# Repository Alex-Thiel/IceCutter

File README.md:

# IceCutter

This is the PCB and Code for the Temperature Controlled Ice Cutter for EEE4022S.

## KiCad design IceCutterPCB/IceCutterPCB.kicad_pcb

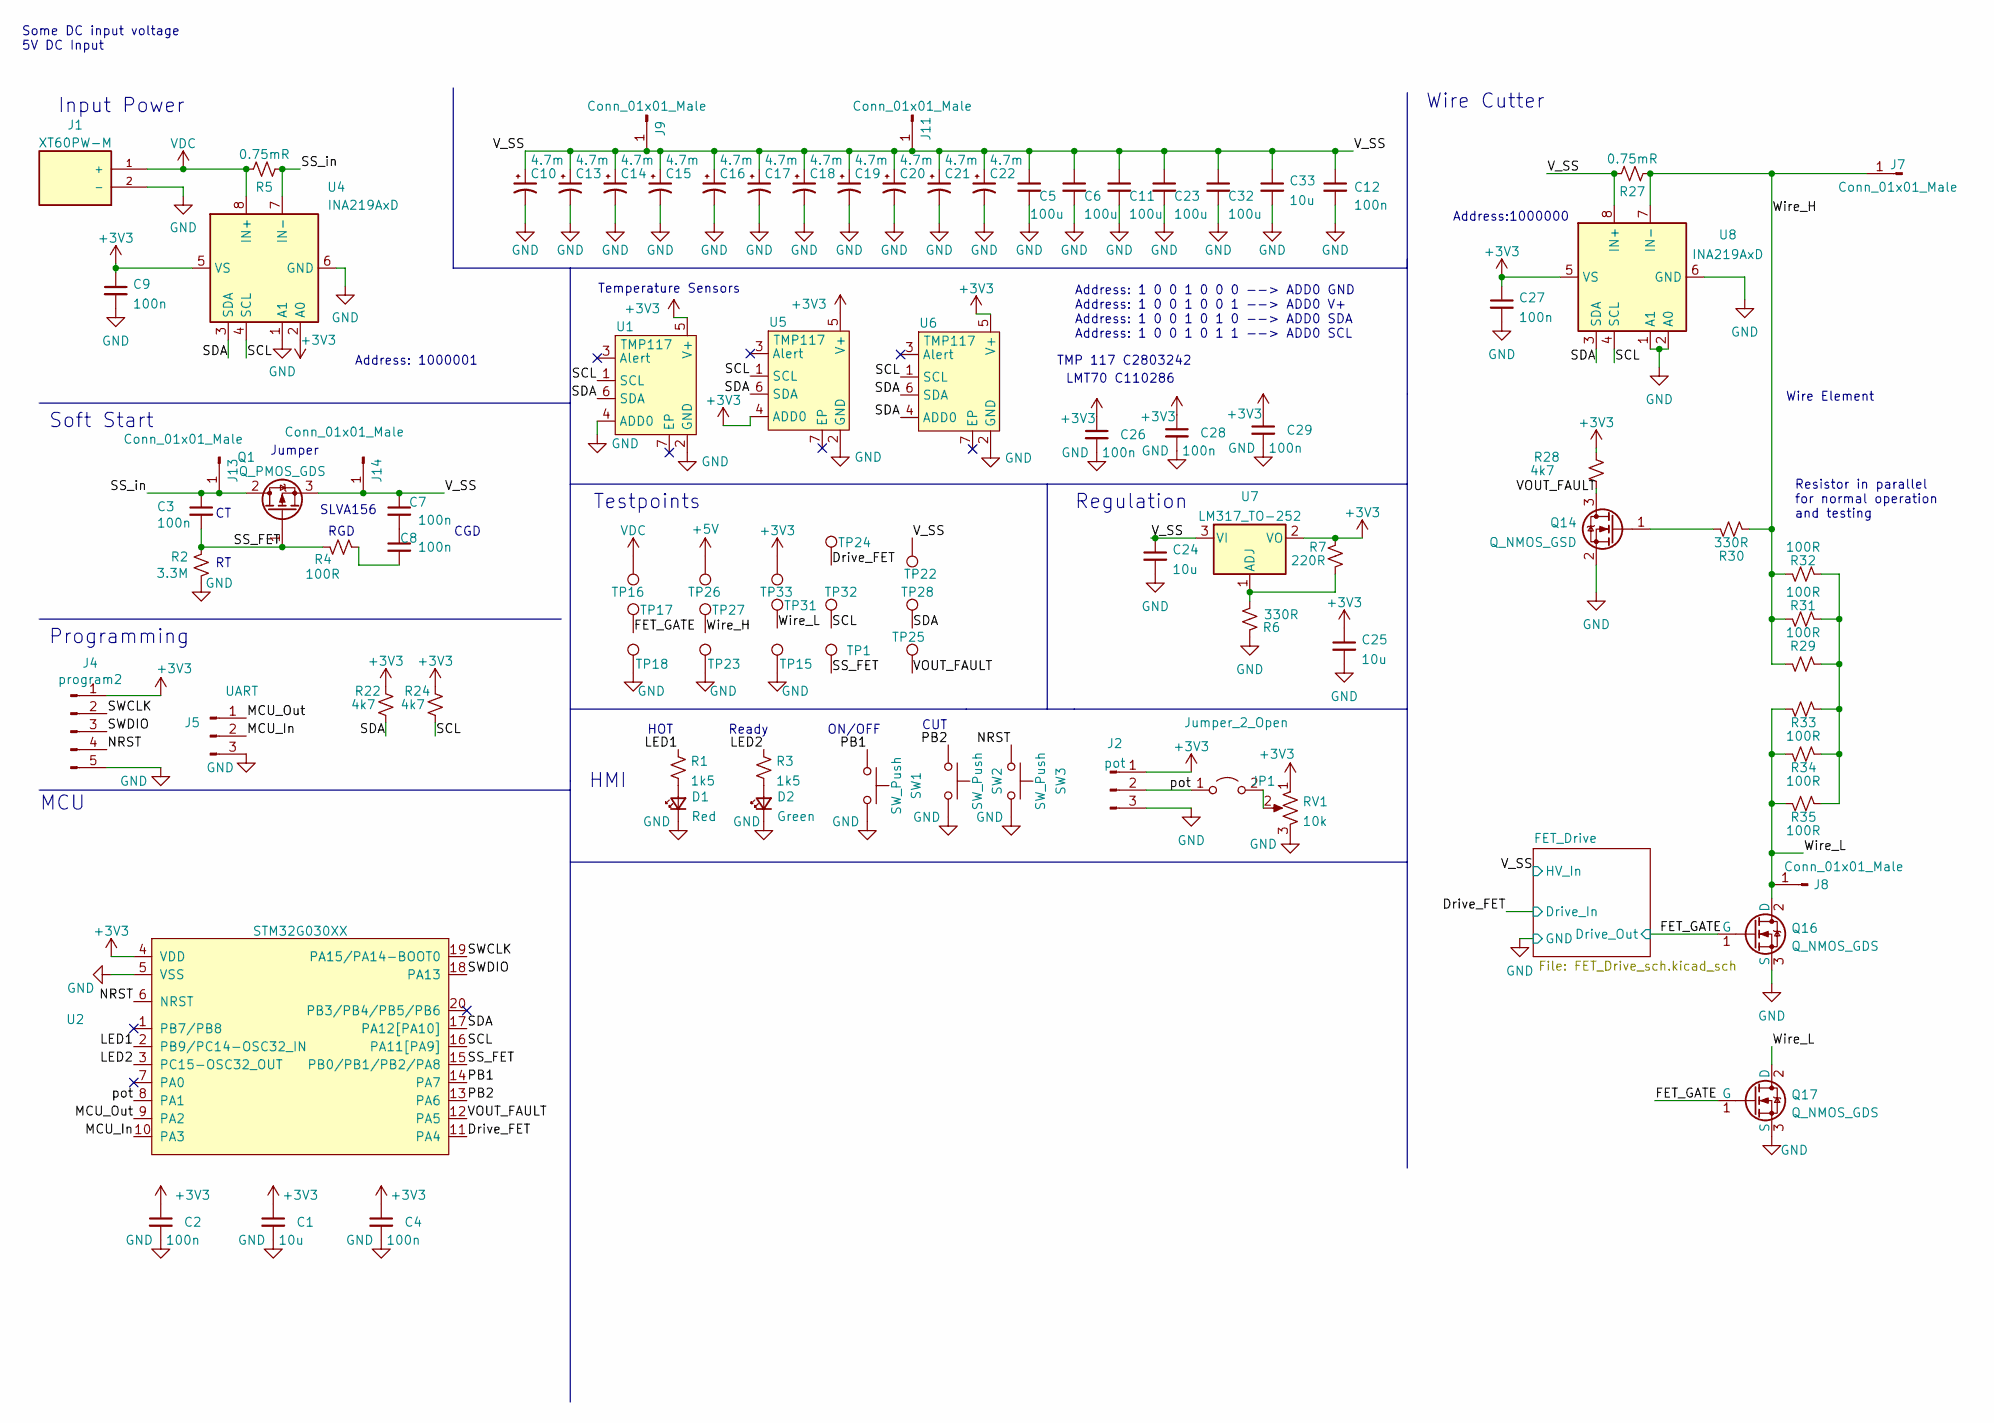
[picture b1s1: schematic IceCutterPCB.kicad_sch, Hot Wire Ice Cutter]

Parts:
C1, C24, C25, C33: 10u; C_0603_1608Metric; LCSC C96446
C2, C3, C4, C7, C8, C9, C12, C26, C27, C28, C29: 100n; C_0402_1005Metric; LCSC C307331
C5, C6, C11, C23, C32: 100u; C_1206_3216Metric; LCSC C15008
C10, C13, C14, C15, C16, C17, C18, C19, C20, C21, C22: 4.7m; CP_Radial_D14.0mm_P5.00mm
D1: Red; D_0603_1608Metric; LCSC C2286
D2: Green; D_0603_1608Metric; LCSC C72043
J1: XT60PW-M; AMASS_XT60PW-M; PARTREV V1.2
J2: pot; PinHeader_1x03_P2.54mm_Vertical
J4: program2; PinHeader_1x05_P2.54mm_Vertical
J5: UART; PinHeader_1x03_P2.54mm_Vertical
J7, J8, J9, J11, J13, J14: Conn_01x01_Male; SMD_Pad_15x10
JP1: Jumper_2_Open; SolderJumper-2_P1.3mm_Open_RoundedPad1.0x1.5mm
Q1: Q_PMOS_GDS; TO-252-2
Q14: Q_NMOS_GSD; SOT-23; LCSC C20917
Q16, Q17: Q_NMOS_GDS; TO-252-2; LCSC C709962
R1, R3: 1k5; R_0402_1005Metric; LCSC C25867
R2: 3.3M; R_0402_1005Metric; LCSC C25741
R4: 100R; R_0402_1005Metric; LCSC C25076
R5, R27: 0.75mR; res_5930
R6, R30: 330R; R_0402_1005Metric; LCSC C25104
R7: 220R; R_0402_1005Metric; LCSC C25091
R22, R24, R28: 4k7; R_0402_1005Metric; LCSC C25900
R29, R31, R32, R33, R34, R35: 100R; R_1206_3216Metric; LCSC C17901
RV1: 10k; RK09_THT_Pot_C209770; LCSC C209770
SW1, SW2, SW3: SW_Push; SW_SPST_TL3342; LCSC C318884
TP1, TP15, TP16, TP17, TP18, TP22, TP23, TP24, TP25, TP26, TP27, TP28, TP31, TP32, TP33: TestPoint; TestPoint_Pad_D2.0mm
U1, U5, U6: TMP117; WSON-6-1EP_2x2mm_P0.65mm_EP1x1.6mm; LCSC C2803242
U2: STM32G030XX; TSSOP-20_4.4x6.5mm_P0.65mm; LCSC C529330
U4, U8: INA219AxD; SOIC-8_3.9x4.9mm_P1.27mm; LCSC C138706
U7: LM317_TO-252; TO-252-2; LCSC C75510

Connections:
+3V3: C1.1, C2.1, C4.1, C9.1, C25.1, C26.1, C27.1, C28.1, C29.1, J2.1, J4.1, R7.2, R22.2, R24.2, R28.2, RV1.1, TP33.1, U1.5 (V+), U2.4 (VDD), U4.2 (A0), U4.5 (VS), U5.4 (ADD0), U5.5 (V+), U6.5 (V+), U7.2 (VO), U8.5 (VS)
+5V: TP26.1
/Drive_FET: TP24.1, U2.11 (PA4); also elsewhere on the board
/FET_GATE: Q16.1 (G), Q17.1 (G), TP17.1; also elsewhere on the board
/LED1: R1.1, U2.2 (PB9/PC14-OSC32_IN)
/LED2: R3.1, U2.3 (PC15-OSC32_OUT)
/MCU_In: J5.2, U2.10 (PA3)
/MCU_Out: J5.1, U2.9 (PA2)
/NRST: J4.4, SW3.1, U2.6 (NRST)
/PB1: SW1.1, U2.14 (PA7)
/PB2: SW2.1, U2.13 (PA6)
/SCL: R24.1, TP32.1, U1.1 (SCL), U2.16 (PA11[PA9]), U4.4 (SCL), U5.1 (SCL), U6.1 (SCL), U8.4 (SCL)
/SDA: R22.1, TP28.1, U1.6 (SDA), U2.17 (PA12[PA10]), U4.3 (SDA), U5.6 (SDA), U6.4 (ADD0), U6.6 (SDA), U8.3 (SDA)
/SS_FET: C3.2, Q1.1 (G), R2.1, R4.1, TP1.1, U2.15 (PB0/PB1/PB2/PA8)
/SS_in: C3.1, J13.1, Q1.2 (D), R5.2, U4.7 (IN-)
/SWCLK: J4.2, U2.19 (PA15/PA14-BOOT0)
/SWDIO: J4.3, U2.18 (PA13)
/VOUT_FAULT: Q14.3 (D), R28.1, TP25.1, U2.12 (PA5)
/V_SS: C5.1, C6.1, C7.1, C10.1, C11.1, C12.1, C13.1, C14.1, C15.1, C16.1, C17.1, C18.1, C19.1, C20.1, C21.1, C22.1, C23.1, C24.1, C32.1, C33.1, J9.1, J11.1, J14.1, Q1.3 (S), R27.1, TP22.1, U7.3 (VI), U8.8 (IN+); also elsewhere on the board
/Wire_H: J7.1, R27.2, R29.1, R30.1, R31.1, R32.1, TP27.1, U8.7 (IN-)
/Wire_L: J8.1, Q16.2 (D), Q17.2 (D), R33.2, R34.2, R35.2, TP31.1
/pot: J2.2, JP1.1 (A), U2.8 (PA1)
GND: C1.2, C2.2, C4.2, C5.2, C6.2, C9.2, C10.2, C11.2, C12.2, C13.2, C14.2, C15.2, C16.2, C17.2, C18.2, C19.2, C20.2, C21.2, C22.2, C23.2, C24.2, C25.2, C26.2, C27.2, C28.2, C29.2, C32.2, C33.2, D1.1 (K), D2.1 (K), J1.2 (-), J2.3, J4.5, J5.3, Q14.2 (S), Q16.3 (S), Q17.3 (S), R2.2, R6.1, RV1.3, SW1.2, SW2.2, SW3.2, TP15.1, TP18.1, TP23.1, U1.2 (GND), U1.4 (ADD0), U2.5 (VSS), U4.1 (A1), U4.6 (GND), U5.2 (GND), U6.2 (GND), U8.1 (A1), U8.2 (A0), U8.6 (GND); also elsewhere on the board
unnamed: C7.2, C8.1
unnamed: C8.2, R4.2
unnamed: D1.2 (A), R1.2
unnamed: D2.2 (A), R3.2
unnamed: JP1.2 (B), RV1.2
unnamed: Q14.1 (G), R30.2
unnamed: R6.2, R7.1, U7.1 (ADJ)
unnamed: R29.2, R31.2, R32.2, R33.1, R34.1, R35.1
VDC: J1.1 (+), R5.1, TP16.1, U4.8 (IN+)

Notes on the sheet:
CUT
Resistor in parallel for normal operation and testing
Some DC input voltage 5V DC Input
CGD
LMT70 C110286
Jumper
Testpoints
HOT
Input Power
Wire Element
HMI
Soft Start
SLVA156
Programming
Address: 1 0 0 1 0 0 0 --> ADD0 GND Address: 1 0 0 1 0 0 1 --> ADD0 V+ Address: 1 0 0 1 0 1 0 --> ADD0 SDA Address: 1 0 0 1 0 1 1 --> ADD0 SCL
Address: 1000001
MCU
Ready
Wire Cutter
ON/OFF
TMP 117 C2803242
Regulation
Address:1000000
Temperature Sensors
RGD

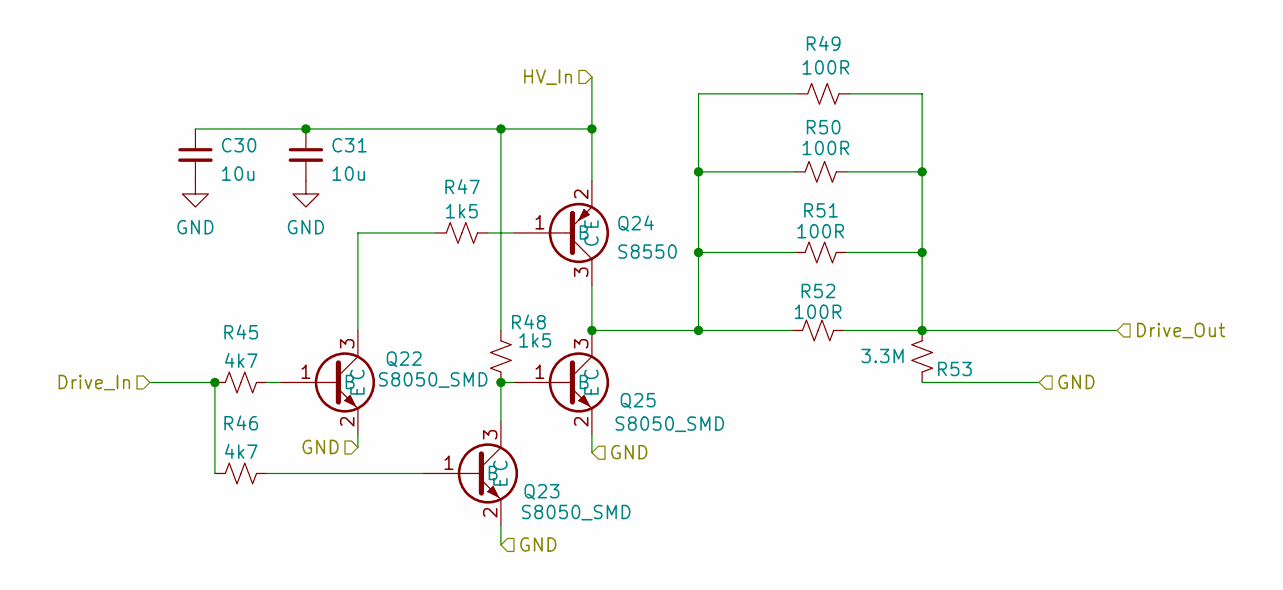
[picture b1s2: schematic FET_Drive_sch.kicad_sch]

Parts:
C30, C31: 10u; C_0603_1608Metric; LCSC C96446
Q22, Q23, Q25: S8050_SMD; SOT-23; LCSC C2150
Q24: S8550; SOT-23; LCSC C8542
R45, R46: 4k7; R_0402_1005Metric; LCSC C25900
R47, R48: 1k5; R_0402_1005Metric; LCSC C25867
R49, R50, R51, R52: 100R; R_0402_1005Metric; LCSC C25076
R53: 3.3M; R_0402_1005Metric; LCSC C25741

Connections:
/Drive_FET: R45.1, R46.1; also elsewhere on the board
/FET_GATE: R49.2, R50.2, R51.2, R52.2, R53.1; also elsewhere on the board
/V_SS: C30.1, C31.1, Q24.2 (E), R48.2; also elsewhere on the board
GND: C30.2, C31.2, Q22.2 (E), Q23.2 (E), Q25.2 (E), R53.2; also elsewhere on the board
unnamed: Q22.1 (B), R45.2
unnamed: Q22.3 (C), R47.1
unnamed: Q23.1 (B), R46.2
unnamed: Q23.3 (C), Q25.1 (B), R48.1
unnamed: Q24.1 (B), R47.2
unnamed: Q24.3 (C), Q25.3 (C), R49.1, R50.1, R51.1, R52.1

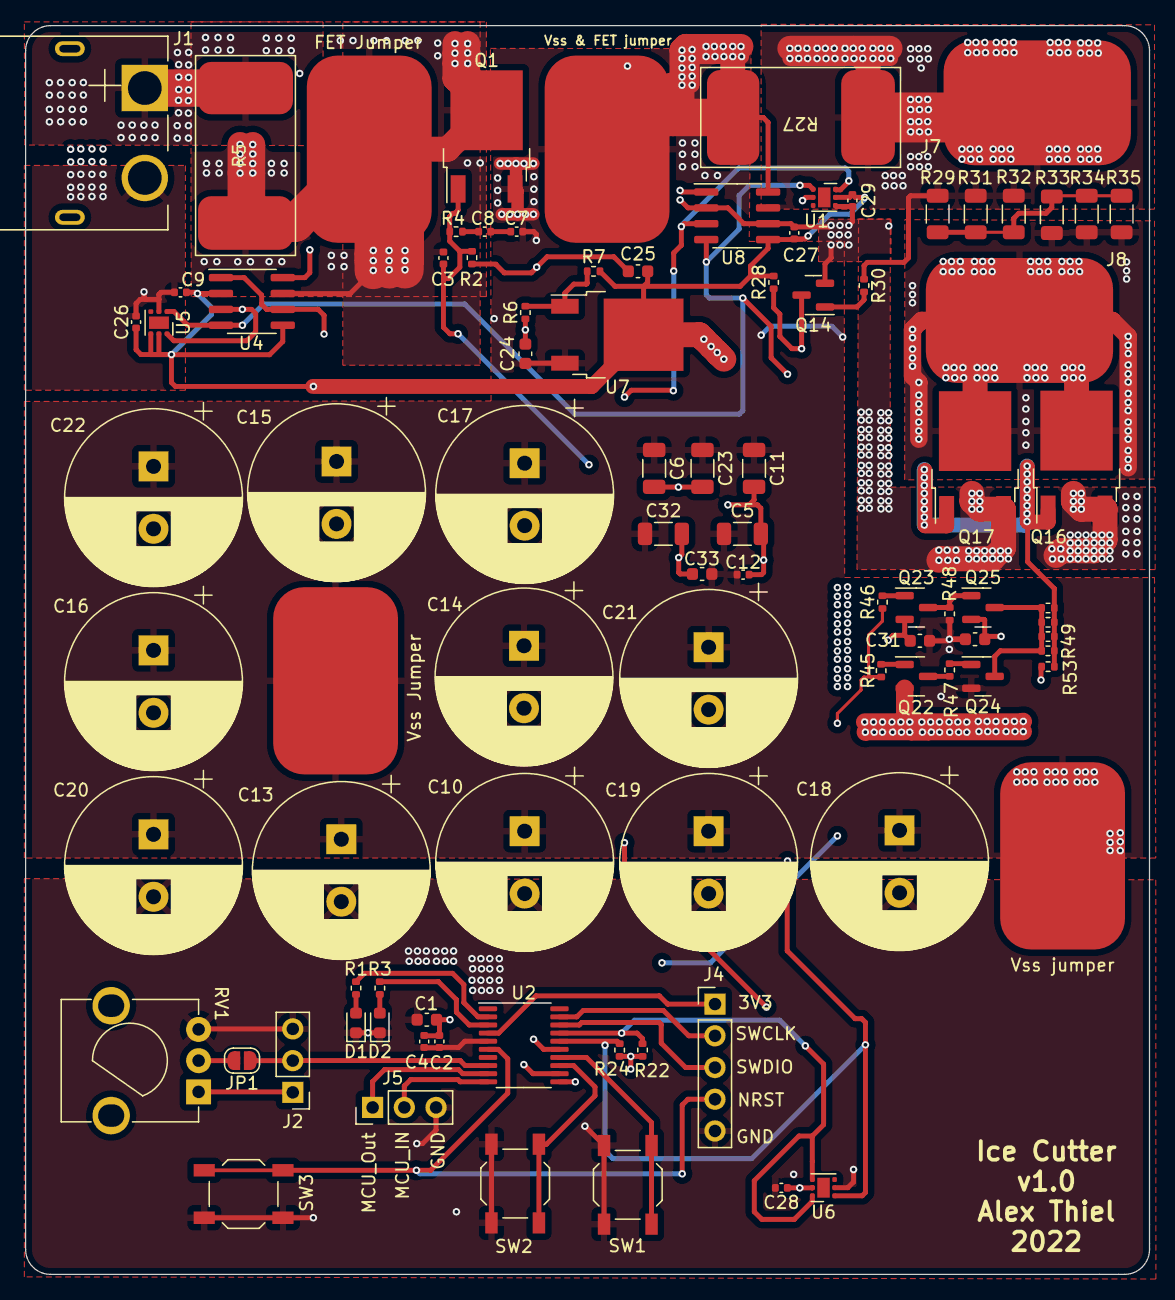
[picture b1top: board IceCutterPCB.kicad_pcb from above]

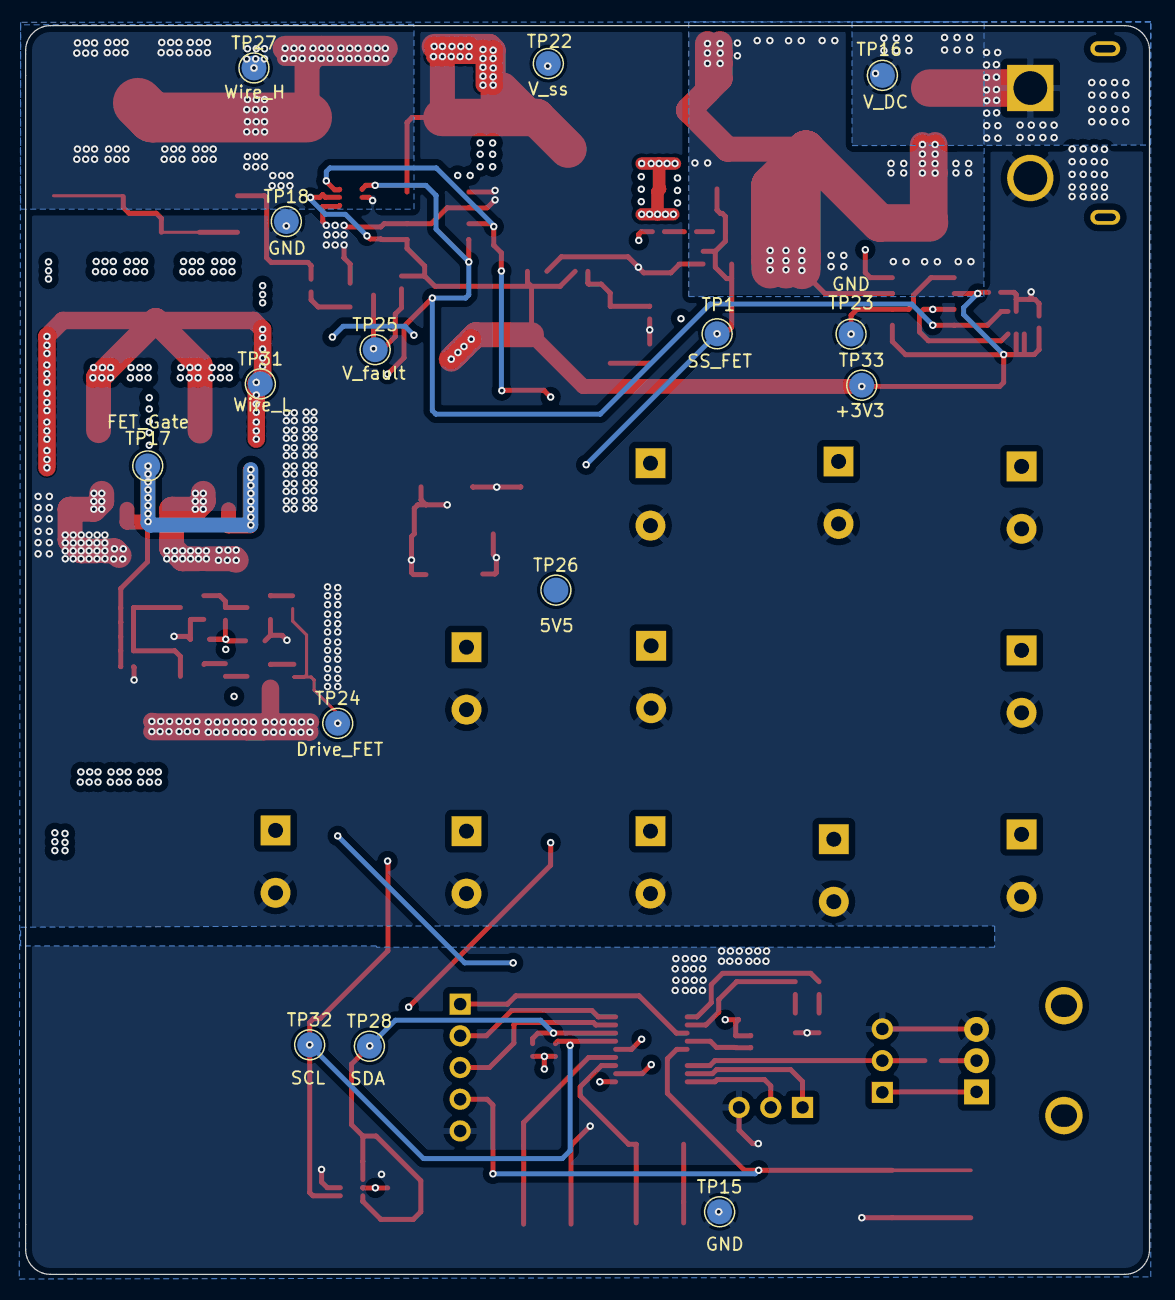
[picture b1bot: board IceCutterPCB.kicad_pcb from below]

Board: 4 copper layers, 90.0 x 100.0 mm, 107 parts (15 on the bottom side), 37 nets.

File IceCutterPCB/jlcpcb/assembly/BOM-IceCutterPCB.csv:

Comment,Designator,Footprint,LCSC
INA219AxD,"U4,U8",SOIC-8_3.9x4.9mm_P1.27mm,C138706
100u,"C11,C23,C32,C5,C6",C_1206_3216Metric,C15008
Q_PMOS_GDS,Q1,TO-252-2,C165222
100R,"R29,R31,R32,R33,R34,R35",R_1206_3216Metric,C17901
Q_NMOS_GSD,Q14,SOT-23,C20917
10k,RV1,RK09_THT_Pot_C209770,C209770
S8050_SMD,"Q22,Q23,Q25",SOT-23,C2150
3.3M,"R2,R53",R_0402_1005Metric,C227368
Red,D1,D_0603_1608Metric,C2286
100R,"R4,R49,R50,R51,R52",R_0402_1005Metric,C25076
220R,R7,R_0402_1005Metric,C25091
330R,"R30,R6",R_0402_1005Metric,C25104
1k5,"R1,R3,R47,R48",R_0402_1005Metric,C25867
4k7,"R22,R24,R28,R45,R46",R_0402_1005Metric,C25900
TMP117,"U1,U5,U6",WSON-6-1EP_2x2mm_P0.65mm_EP1x1.6mm,C2803242
100n,"C12,C2,C26,C27,C28,C29,C3,C4,C7,C8,C9",C_0402_1005Metric,C307331
SW_Push,"SW1,SW2,SW3",SW_SPST_TL3342,C318884
0.75mR,"R27,R5",res_5930,C495778
STM32G030XX,U2,TSSOP-20_4.4x6.5mm_P0.65mm,C529330
Q_NMOS_GDS,"Q16,Q17",TO-252-2,C709962
Green,D2,D_0603_1608Metric,C72043
LM317_TO-252,U7,TO-252-2,C75510
S8550,Q24,SOT-23,C8542
10u,"C1,C24,C25,C30,C31,C33",C_0603_1608Metric,C96446
XT60PW-M,J1,AMASS_XT60PW-M,C98732

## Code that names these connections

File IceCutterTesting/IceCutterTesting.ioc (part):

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Mcu.Name=STM32G030F6Px
Mcu.Package=TSSOP20
Mcu.UserName=STM32G030F6Px
PA1.Mode=IN1
PA1.Signal=ADC1_IN1
PA11\ [PA9].Mode=I2C
PA11\ [PA9].Signal=I2C2_SCL
PA12\ [PA10].Mode=I2C
PA12\ [PA10].Signal=I2C2_SDA
PA13.Mode=Serial_Wire
PA13.Signal=SYS_SWDIO
PA14-BOOT0.Mode=Serial_Wire
PA14-BOOT0.Signal=SYS_SWCLK
PA14-BOOT0__PA15.StandardMode=true
PA2.Mode=Asynchronous
PA2.Signal=USART2_TX
PA3.Mode=Asynchronous
PA3.Signal=USART2_RX
PA4.Signal=S_TIM14_CH1
PA5.Signal=GPIO_Input
PA6.GPIOParameters=GPIO_PuPd,GPIO_ModeDefaultEXTI
PA6.GPIO_ModeDefaultEXTI=GPIO_MODE_IT_FALLING
PA6.GPIO_PuPd=GPIO_PULLUP
PA6.Signal=GPXTI6
PA7.GPIOParameters=GPIO_PuPd,GPIO_ModeDefaultEXTI
PA7.GPIO_ModeDefaultEXTI=GPIO_MODE_IT_FALLING
PA7.GPIO_PuPd=GPIO_PULLUP
PA7.Signal=GPXTI7
PB0.GPIOParameters=GPIO_Speed,PinState
PB0.GPIO_Speed=GPIO_SPEED_FREQ_VERY_HIGH
PB0.PinState=GPIO_PIN_SET
PB0.Signal=GPIO_Output
PB0__PB1__PB2__PA8.StandardMode=true
PB3__PB4__PB5__PB6.StandardMode=true
PB5.Signal=S_TIM3_CH2
PB7__PB8.StandardMode=true
PB9.GPIOParameters=GPIO_Speed,PinState,GPIO_PuPd,GPIO_ModeDefaultOutputPP,GPIO_FM9
PB9.GPIO_FM9=SYSCFG_FASTMODEPLUS_PB9
PB9.GPIO_ModeDefaultOutputPP=GPIO_MODE_OUTPUT_PP
PB9.GPIO_PuPd=GPIO_NOPULL
PB9.GPIO_Speed=GPIO_SPEED_FREQ_VERY_HIGH
PB9.PinState=GPIO_PIN_SET
PB9.Signal=GPIO_Output
PC14-OSC32_IN\ (PC14)__PB9.StandardMode=true
PC15-OSC32_OUT\ (PC15).GPIOParameters=PinState,GPIO_PuPd,GPIO_ModeDefaultOutputPP
PC15-OSC32_OUT\ (PC15).GPIO_ModeDefaultOutputPP=GPIO_MODE_OUTPUT_PP
PC15-OSC32_OUT\ (PC15).GPIO_PuPd=GPIO_PULLUP
PC15-OSC32_OUT\ (PC15).PinState=GPIO_PIN_SET
PC15-OSC32_OUT\ (PC15).Signal=GPIO_Output
RCC.HSE_VALUE=8000000
RCC.SYSCLKFreq_VALUE=16000000
board=custom

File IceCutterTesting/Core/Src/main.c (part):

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#define RED_LED_state	GPIOB
#define GREEN_LED 		GPIO_PIN_15
#define GREEN_LED_state	GPIOC
#define SS_FET			GPIO_PIN_0
#define SS_FET_state	GPIOB
#define DRIVE_FET 		GPIO_PIN_4
#define DRIVE_FET_state	GPIOA
#define SW2 			GPIO_PIN_6
#define SW2_state		GPIOA
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
  //current_state = POWER_ON;
  startup_initialisation();
  HAL_GPIO_WritePin(GPIOB,SS_FET,GPIO_PIN_SET);
  /* USER CODE END 2 */

  /* Infinite loop */
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  /*Configure GPIO pin Output Level */
  HAL_GPIO_WritePin(GPIOC, GPIO_PIN_15, GPIO_PIN_SET);

  /*Configure GPIO pins : PB9 PB0 */
  GPIO_InitStruct.Pin = GPIO_PIN_9|GPIO_PIN_0;
  GPIO_InitStruct.Mode = GPIO_MODE_OUTPUT_PP;
  GPIO_InitStruct.Pull = GPIO_NOPULL;
  GPIO_InitStruct.Speed = GPIO_SPEED_FREQ_VERY_HIGH;
  HAL_GPIO_Init(GPIOB, &GPIO_InitStruct);

  /*Configure GPIO pin : PC15 */
  GPIO_InitStruct.Pin = GPIO_PIN_15;
  GPIO_InitStruct.Mode = GPIO_MODE_OUTPUT_PP;
  GPIO_InitStruct.Pull = GPIO_PULLUP;
  GPIO_InitStruct.Speed = GPIO_SPEED_FREQ_LOW;
  HAL_GPIO_Init(GPIOC, &GPIO_InitStruct);

  /*Configure GPIO pin : PA5 */
  GPIO_InitStruct.Pin = GPIO_PIN_5;
  GPIO_InitStruct.Mode = GPIO_MODE_INPUT;
  GPIO_InitStruct.Pull = GPIO_NOPULL;
  HAL_GPIO_Init(GPIOA, &GPIO_InitStruct);

  /*Configure GPIO pins : PA6 PA7 */
  GPIO_InitStruct.Pin = GPIO_PIN_6|GPIO_PIN_7;
  GPIO_InitStruct.Mode = GPIO_MODE_IT_FALLING;
  GPIO_InitStruct.Pull = GPIO_PULLUP;
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 */
 void SS_charge(){
	 uint8_t counter = 0;
	 HAL_GPIO_WritePin(GPIOB,SS_FET,GPIO_PIN_RESET);
	 while(HAL_GPIO_ReadPin(GPIOB,SS_FET) == GPIO_PIN_RESET){
		 float input_current = current_input;//measure_current(INPUT_INA219);
		 if(input_current >= MAX_INRUSH_CURRENT && counter == 0){
			 HAL_GPIO_WritePin(GPIOB,SS_FET, GPIO_PIN_SET); //stop charging caps
			 counter = counter + 1;
			 HAL_GPIO_WritePin(GPIOB,SS_FET, GPIO_PIN_RESET); //stop charging caps
		 }else if(input_current >= MAX_INRUSH_CURRENT && counter >=1){
			 HAL_GPIO_WritePin(GPIOB,SS_FET, GPIO_PIN_SET); //stop charging caps
			 counter = counter + 1;
			 pulse_charge_SS();
		 }else if(temp_checks() == ABOVE_THRESHOLD){
			 HAL_GPIO_WritePin(GPIOB,SS_FET, GPIO_PIN_SET); //stop charging caps
			 while(temp_checks()==ABOVE_THRESHOLD){
				 HAL_Delay(100); //allow time for board to cool
			 }
			 HAL_GPIO_WritePin(GPIOB,SS_FET,GPIO_PIN_RESET);
		 }else if(current_input == 0){// measure_current(INPUT_INA219)==0  capacitors fully charged, no current flow
			 HAL_GPIO_WritePin(GPIOB,SS_FET, GPIO_PIN_SET);//stop soft start circuit charging caps
			 break;
		 }
		 UART_output();
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 }

 /**
   * @brief	Uses SS_FET connection to micro-controller to increase time constant of soft-start circuit to reduce inrush current
   * @param
   * @retval
 */
 void pulse_charge_SS(){
	   for (uint8_t i = 1; i < 50; ++i)
	     {
		   HAL_GPIO_WritePin(GPIOB,SS_FET,GPIO_PIN_RESET);
		   HAL_Delay(0.05);
		   HAL_GPIO_WritePin(GPIOB,SS_FET,GPIO_PIN_SET);
	     }
	   HAL_GPIO_WritePin(GPIOB,SS_FET,GPIO_PIN_RESET);
 }

/** @brief	Use soft-start circuit to charge capacitors, green LED turned on once capacitors fully charged
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	 	HAL_GPIO_WritePin(RED_LED_state, RED_LED, GPIO_PIN_SET);//turn on red led
	 	HAL_GPIO_WritePin(GREEN_LED_state, GREEN_LED, GPIO_PIN_RESET);//turn off green led
	 	set_PWM_driveFET(0);//ensure heating wire doesn't conduct
		HAL_GPIO_WritePin(GPIOB,SS_FET,GPIO_PIN_SET); //keep SS_FET high, soft start stops Caps charging
		ina_initialise();//set config registers of INA219s
	   //prompt user for reference temp input via UART
	   //once got input, shut down interrupt channel
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		   temps_in_range = temp_checks();
	   }
	   SS_charge();
	   HAL_GPIO_WritePin(GPIOB,SS_FET, GPIO_PIN_SET);//allow SS_FET to conduct to keep caps charged
	   HAL_GPIO_WritePin(GPIOC, GREEN_LED, GPIO_PIN_SET); // green LED2 turn on, system ready to cut
	   current_state = INITIALISED;
	   //UART_output();
 }
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
	switch(GPIO_Pin){
	case SW1:
		//HAL_GPIO_WritePin(GPIOB,SS_FET,GPIO_PIN_RESET);
		switch (current_state){
		case STEADY_STATE:
			current_state = CUTTING;
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
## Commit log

2022-10-09 Added code
2022-10-09 Added PCB
2022-10-10 Added Operation Procedure
2022-10-10 Added cooling controller
2022-10-10 Changed UART to global variables
2022-10-10 Added button procedure
2022-10-10 Interrupt flags being cleared correctly
2022-10-11 Added while(1) procedure
2022-10-12 Changed GPIO pins to new board
2022-10-13 Added Copper TCR
2022-10-16 Added input current monitoring
2022-10-16 Working current display
2022-10-16 End of day changes
2022-10-17 Changed PWM to interrupt
2022-10-18 Added temp error handling
2022-10-18 Altered current measuring timing
2022-10-18 converted buttons to pull-up resistors
2022-10-19 Semi-functional freq. and pulse modulation with 5ms on time
2022-10-20 Working 2.15ms current reading delay
2022-10-20 Working 4.7678ms measurement delay
2022-10-20 Measuring wire output voltage, duty cycle linked to pot
2022-10-21 check conversion bit and says when not conducting
2022-10-24 Working variable pulse & frequency
2022-10-25 Before attempting to implement controller
2022-10-25 Working controller, Kd =5 Ki = 0.00002
2022-10-31 Final controller design with derivative gain

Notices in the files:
IceCutterTesting/Core/Src/main.c:
Copyright (c) 2022 STMicroelectronics.
All rights reserved.
This software is licensed under terms that can be found in the LICENSE file
